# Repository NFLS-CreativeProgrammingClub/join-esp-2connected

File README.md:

# join-esp-2connected
## 本项目开源，但是不允许商业，您可以随意更改，但是您更改后发布也请开源
> 一个很简单的双esp32开发板
使用uart或者两个io口链接（i2c什么的就可以），mpython有链接函数。针脚全引出，usb已经差分了，上拉电阻也搞了，有一个5v转3.3v模块，使用usb供电。wifi天线什么的也都在外面，用内置天线。

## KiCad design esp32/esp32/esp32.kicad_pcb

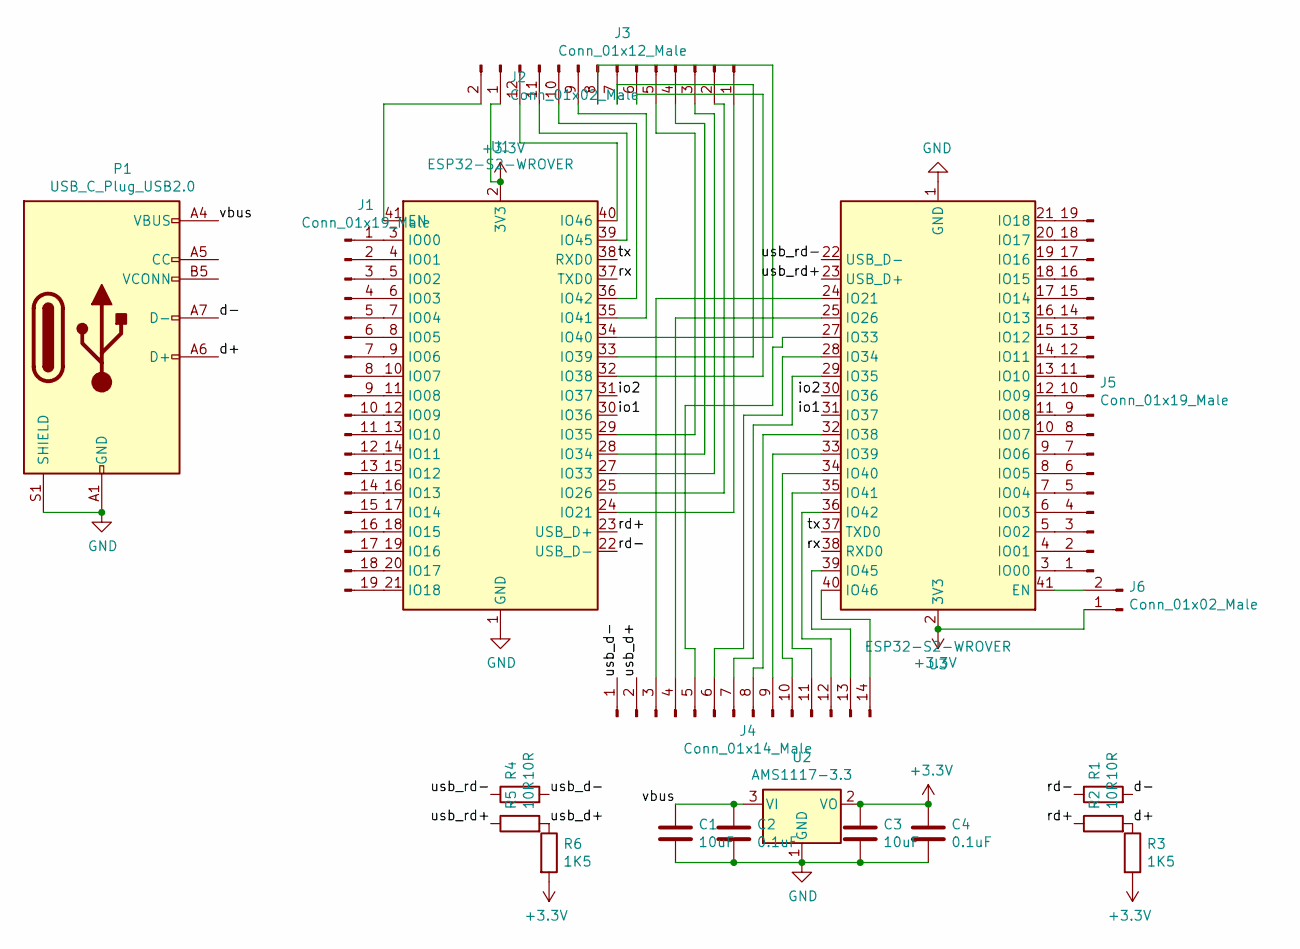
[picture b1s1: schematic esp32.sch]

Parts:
C1, C3: 10uF; C_0402_1005Metric_Pad0.74x0.62mm_HandSolder
C2, C4: 0.1uF; C_0402_1005Metric_Pad0.74x0.62mm_HandSolder
J1, J5: Conn_01x19_Male; PinSocket_1x19_P2.54mm_Vertical
J2, J6: Conn_01x02_Male; PinSocket_1x02_P2.54mm_Vertical
J3: Conn_01x12_Male; PinSocket_1x12_P2.54mm_Vertical
J4: Conn_01x14_Male; PinSocket_1x14_P2.54mm_Vertical
P1: USB_C_Plug_USB2.0; USB_C_Receptacle_GCT_USB4085
R1, R2, R4, R5: 10R; R_0402_1005Metric
R3, R6: 1K5; R_0402_1005Metric
U1, U3: ESP32-S2-WROVER
U2: AMS1117-3.3; SOT-223-3_TabPin2

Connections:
+3V3: C3.1, C4.1, J2.1, J6.1, R3.2, R6.2, U1.2 (3V3), U2.2 (VO), U3.2 (3V3)
/d+: P1.A6 (D+), R2.2, R3.1
/d-: P1.A7 (D-), R1.2
/io1: U1.30 (IO36), U3.31 (IO37)
/io2: U1.31 (IO37), U3.30 (IO36)
/rd+: R2.1, U1.23 (USB_D+)
/rd-: R1.1, U1.22 (USB_D-)
/rx: U1.37 (TXD0), U3.38 (RXD0)
/tx: U1.38 (RXD0), U3.37 (TXD0)
/usb_d+: J4.2, R5.2, R6.1
/usb_d-: J4.1, R4.2
/usb_rd+: R5.1, U3.23 (USB_D+)
/usb_rd-: R4.1, U3.22 (USB_D-)
/vbus: C1.1, C2.1, P1.A4 (VBUS), P1.A9 (VBUS), P1.B4 (VBUS), P1.B9 (VBUS), U2.3 (VI)
GND: C1.2, C2.2, C3.2, C4.2, P1.A1 (GND), P1.A12 (GND), P1.B1 (GND), P1.B12 (GND), P1.S1 (SHIELD), U1.1 (GND), U1.26 (GND), U1.42 (GND), U1.43 (GND), U2.1 (GND), U3.1 (GND), U3.26 (GND), U3.42 (GND), U3.43 (GND)
unnamed: J1.1, U1.3 (IO00)
unnamed: J1.2, U1.4 (IO01)
unnamed: J1.3, U1.5 (IO02)
unnamed: J1.4, U1.6 (IO03)
unnamed: J1.5, U1.7 (IO04)
unnamed: J1.6, U1.8 (IO05)
unnamed: J1.7, U1.9 (IO06)
unnamed: J1.8, U1.10 (IO07)
unnamed: J1.9, U1.11 (IO08)
unnamed: J1.10, U1.12 (IO09)
unnamed: J1.11, U1.13 (IO10)
unnamed: J1.12, U1.14 (IO11)
unnamed: J1.13, U1.15 (IO12)
unnamed: J1.14, U1.16 (IO13)
unnamed: J1.15, U1.17 (IO14)
unnamed: J1.16, U1.18 (IO15)
unnamed: J1.17, U1.19 (IO16)
unnamed: J1.18, U1.20 (IO17)
unnamed: J1.19, U1.21 (IO18)
unnamed: J2.2, U1.41 (EN)
unnamed: J3.1, U1.24 (IO21)
unnamed: J3.2, U1.25 (IO26)
unnamed: J3.3, U1.27 (IO33)
unnamed: J3.4, U1.28 (IO34)
unnamed: J3.5, U1.29 (IO35)
unnamed: J3.6, U1.32 (IO38)
unnamed: J3.7, U1.33 (IO39)
unnamed: J3.8, U1.34 (IO40)
unnamed: J3.9, U1.35 (IO41)
unnamed: J3.10, U1.36 (IO42)
unnamed: J3.11, U1.39 (IO45)
unnamed: J3.12, U1.40 (IO46)
unnamed: J4.3, U3.24 (IO21)
unnamed: J4.4, U3.25 (IO26)
unnamed: J4.5, U3.27 (IO33)
unnamed: J4.6, U3.28 (IO34)
unnamed: J4.7, U3.29 (IO35)
unnamed: J4.8, U3.32 (IO38)
unnamed: J4.9, U3.33 (IO39)
unnamed: J4.10, U3.34 (IO40)
unnamed: J4.11, U3.35 (IO41)
unnamed: J4.12, U3.36 (IO42)
unnamed: J4.13, U3.39 (IO45)
unnamed: J4.14, U3.40 (IO46)
unnamed: J5.1, U3.3 (IO00)
unnamed: J5.2, U3.4 (IO01)
unnamed: J5.3, U3.5 (IO02)
unnamed: J5.4, U3.6 (IO03)
unnamed: J5.5, U3.7 (IO04)
unnamed: J5.6, U3.8 (IO05)
unnamed: J5.7, U3.9 (IO06)
unnamed: J5.8, U3.10 (IO07)
unnamed: J5.9, U3.11 (IO08)
unnamed: J5.10, U3.12 (IO09)
unnamed: J5.11, U3.13 (IO10)
unnamed: J5.12, U3.14 (IO11)
unnamed: J5.13, U3.15 (IO12)
unnamed: J5.14, U3.16 (IO13)
unnamed: J5.15, U3.17 (IO14)
unnamed: J5.16, U3.18 (IO15)
unnamed: J5.17, U3.19 (IO16)
unnamed: J5.18, U3.20 (IO17)
unnamed: J5.19, U3.21 (IO18)
unnamed: J6.2, U3.41 (EN)

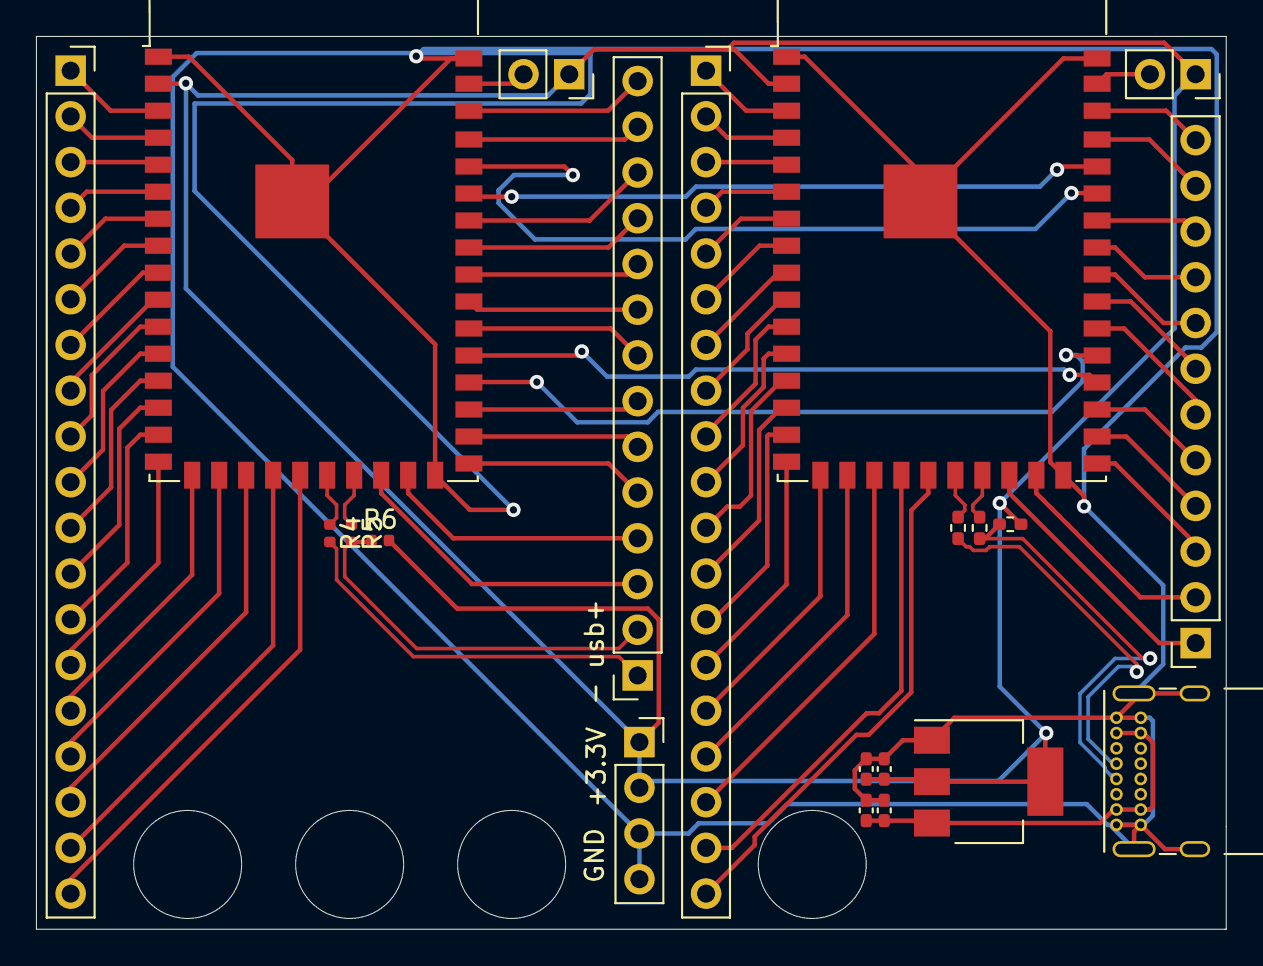
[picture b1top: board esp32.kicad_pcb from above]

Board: 2 copper layers, 66.1 x 49.6 mm, 20 parts (0 on the bottom side), 79 nets.

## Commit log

2020-10-09 初始
    使用uart或者两个io口链接（i2c什么的就可以），mpython有链接函数。针脚全引出，usb已经差分了，但是没有在d+上上拉电阻，可以上拉一个10k电阻，有一个5v转3.3v模块，使用usb供电。wifi天线什么的也都在外面，用内置天线。
2020-10-15 第二次更新
    稍微优化了一下下
